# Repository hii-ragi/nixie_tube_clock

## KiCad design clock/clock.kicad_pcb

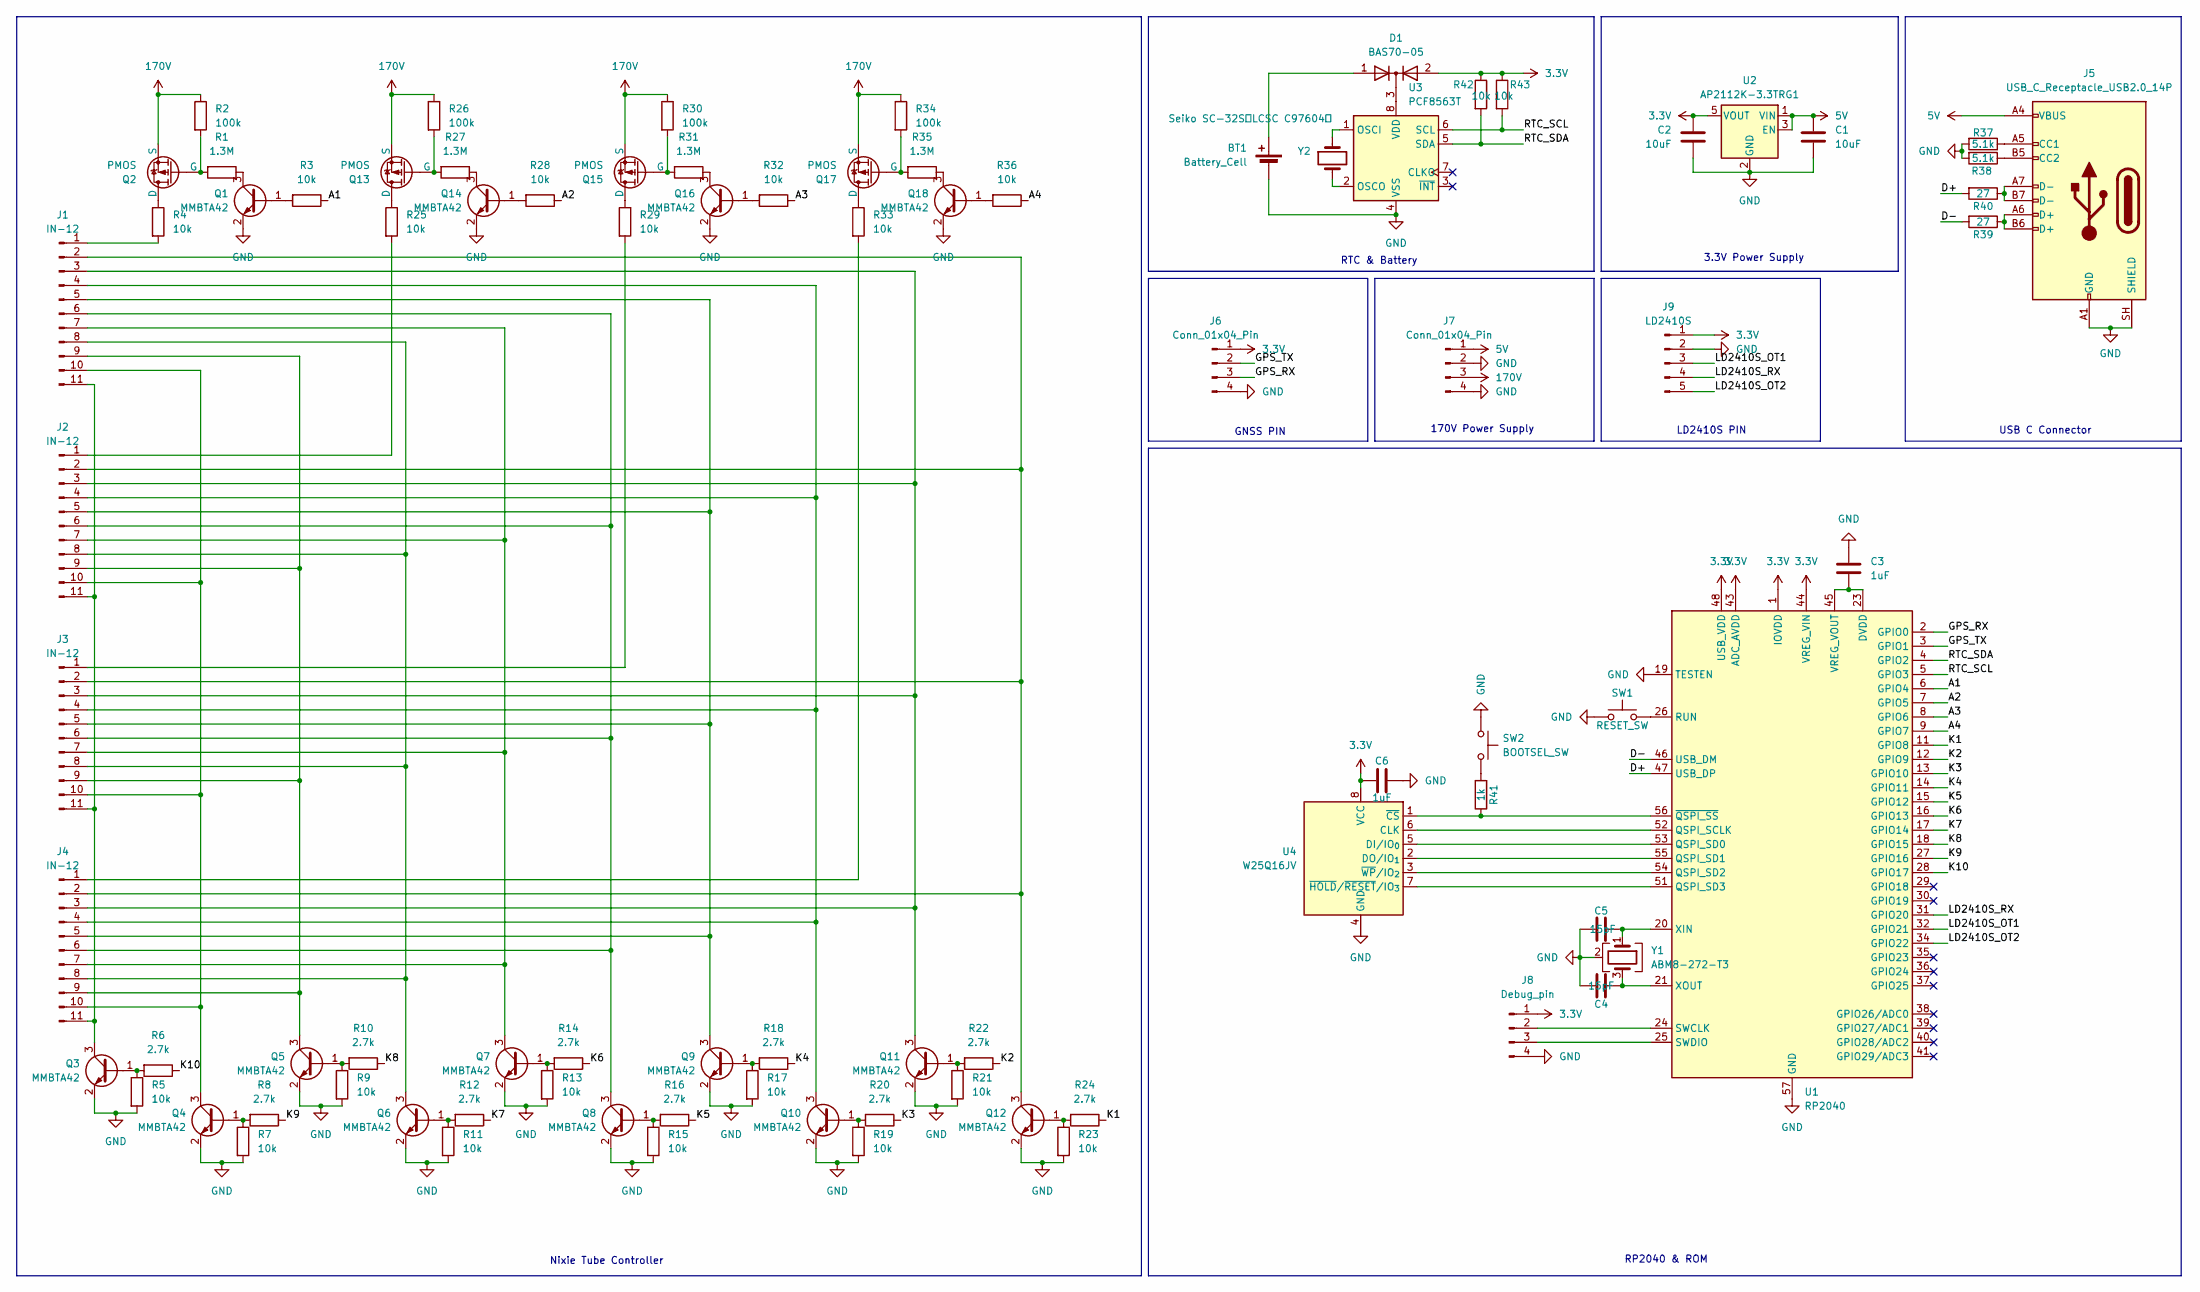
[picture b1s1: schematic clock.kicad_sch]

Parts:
BT1: Battery_Cell
C1, C2: 10uF; C_0603_1608Metric
C3, C6: 1uF; C_0603_1608Metric
C4, C5: 15pF; C_0603_1608Metric
D1: BAS70-05; SOT-23
J1, J2, J3, J4: IN-12
J5: USB_C_Receptacle_USB2.0_14P; USB_C_Receptacle_Palconn_UTC16-G
J6, J7: Conn_01x04_Pin; PinSocket_1x04_P2.54mm_Vertical
J8: Debug_pin; PinSocket_1x04_P2.54mm_Vertical
J9: LD2410S; PinSocket_1x05_P2.54mm_Vertical
Q1, Q3, Q4, Q5, Q6, Q7, Q8, Q9, Q10, Q11, Q12, Q14, Q16, Q18: MMBTA42; SOT-23
Q2, Q13, Q15, Q17: PMOS; SC-59
R1, R27, R31, R35: 1.3M; R_0603_1608Metric
R2, R26, R30, R34: 100k; R_0603_1608Metric
R3, R4, R5, R7, R9, R11, R13, R15, R17, R19, R21, R23, R25, R28, R29, R32, R33, R36, R42, R43: 10k; R_0603_1608Metric
R6, R8, R10, R12, R14, R16, R18, R20, R22, R24: 2.7k; R_0603_1608Metric
R37, R38: 5.1k; R_0603_1608Metric
R39, R40: 27; R_0603_1608Metric
R41: 1k; R_0603_1608Metric
SW1: RESET_SW; SW-SMD_4P-L5.1-W5.1-P3.70-LS6.5-TL_H1.5
SW2: BOOTSEL_SW; SW-SMD_4P-L5.1-W5.1-P3.70-LS6.5-TL_H1.5
U1: RP2040; QFN-56-1EP_7x7mm_P0.4mm_EP3.2x3.2mm
U2: AP2112K-3.3TRG1; SOT-23-5
U3: PCF8563T; SOIC-8_3.9x4.9mm_P1.27mm
U4: W25Q16JV; SOIC-8_5.3x5.3mm_P1.27mm
Y1: ABM8-272-T3; Crystal_SMD_0603-4Pin_6.0x3.5mm
Y2: Seiko SC-32S（LCSC C97604）; Crystal_AT310_D3.0mm_L10.0mm_Horizontal

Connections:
3.3V: C2.1, C6.2, D1.2 (A), J6.1, J8.1, J9.1, R42.1, R43.1, U1.1 (IOVDD), U1.10 (IOVDD), U1.22 (IOVDD), U1.33 (IOVDD), U1.42 (IOVDD), U1.43 (ADC_AVDD), U1.44 (VREG_VIN), U1.48 (USB_VDD), U1.49 (IOVDD), U2.5 (VOUT), U4.8 (VCC)
5V: C1.1, J5.A4 (VBUS), J5.A9 (VBUS), J5.B4 (VBUS), J5.B9 (VBUS), J7.1, U2.1 (VIN), U2.3 (EN)
170V: J7.3, Q2.3 (S), Q13.3 (S), Q15.3 (S), Q17.3 (S), R2.1, R26.1, R30.1, R34.1
/A1: R3.1, U1.6 (GPIO4)
/A2: R28.1, U1.7 (GPIO5)
/A3: R32.1, U1.8 (GPIO6)
/A4: R36.1, U1.9 (GPIO7)
/D+: R40.2, U1.47 (USB_DP)
/D-: R39.2, U1.46 (USB_DM)
/GPS_RX: J6.3, U1.2 (GPIO0)
/GPS_TX: J6.2, U1.3 (GPIO1)
/K1: R24.1, U1.11 (GPIO8)
/K2: R22.1, U1.12 (GPIO9)
/K3: R20.1, U1.13 (GPIO10)
/K4: R18.1, U1.14 (GPIO11)
/K5: R16.1, U1.15 (GPIO12)
/K6: R14.1, U1.16 (GPIO13)
/K7: R12.1, U1.17 (GPIO14)
/K8: R10.1, U1.18 (GPIO15)
/K9: R8.1, U1.27 (GPIO16)
/K10: R6.1, U1.28 (GPIO17)
/LD2410S_OT1: J9.3, U1.32 (GPIO21)
/LD2410S_OT2: J9.5, U1.34 (GPIO22)
/LD2410S_RX: J9.4, U1.31 (GPIO20)
/RTC_SCL: R43.2, U1.5 (GPIO3), U3.6 (SCL)
/RTC_SDA: R42.2, U1.4 (GPIO2), U3.5 (SDA)
GND: BT1.2 (-), C1.2, C2.2, C3.1, C4.2, C5.2, C6.1, J5.A1 (GND), J5.A12 (GND), J5.B1 (GND), J5.B12 (GND), J5.SH (SHIELD), J6.4, J7.2, J7.4, J8.4, J9.2, Q1.2 (E), Q3.2 (E), Q4.2 (E), Q5.2 (E), Q6.2 (E), Q7.2 (E), Q8.2 (E), Q9.2 (E), Q10.2 (E), Q11.2 (E), Q12.2 (E), Q14.2 (E), Q16.2 (E), Q18.2 (E), R5.2, R7.2, R9.2, R11.2, R13.2, R15.2, R17.2, R19.2, R21.2, R23.2, R37.2, R38.2, SW1.1, SW2.1, U1.19 (TESTEN), U1.57 (GND), U2.2 (GND), U3.4 (VSS), U4.4 (GND), Y1.2 (G), Y1.4 (G)
unnamed: BT1.1 (+), D1.1 (A)
unnamed: D1.3 (K), U3.8 (VDD)
unnamed: J1.1, R4.2
unnamed: J1.2, J2.2, J3.2, J4.2, Q12.3 (C)
unnamed: J1.3, J2.3, J3.3, J4.3, Q11.3 (C)
unnamed: J1.4, J2.4, J3.4, J4.4, Q10.3 (C)
unnamed: J1.5, J2.5, J3.5, J4.5, Q9.3 (C)
unnamed: J1.6, J2.6, J3.6, J4.6, Q8.3 (C)
unnamed: J1.7, J2.7, J3.7, J4.7, Q7.3 (C)
unnamed: J1.8, J2.8, J3.8, J4.8, Q6.3 (C)
unnamed: J1.9, J2.9, J3.9, J4.9, Q5.3 (C)
unnamed: J1.10, J2.10, J3.10, J4.10, Q4.3 (C)
unnamed: J1.11, J2.11, J3.11, J4.11, Q3.3 (C)
unnamed: J2.1, R25.2
unnamed: J3.1, R29.2
unnamed: J4.1, R33.2
unnamed: J5.A5 (CC1), R37.1
unnamed: J5.B5 (CC2), R38.1
unnamed: J5.A6 (D+), J5.B6 (D+), R39.1
unnamed: J5.A7 (D-), J5.B7 (D-), R40.1
unnamed: J8.2, U1.24 (SWCLK)
unnamed: J8.3, U1.25 (SWDIO)
unnamed: Q1.1 (B), R3.2
unnamed: Q1.3 (C), R1.1
unnamed: Q2.1 (D), R4.1
unnamed: Q2.2 (G), R1.2, R2.2
unnamed: Q3.1 (B), R5.1, R6.2
unnamed: Q4.1 (B), R7.1, R8.2
unnamed: Q5.1 (B), R9.1, R10.2
unnamed: Q6.1 (B), R11.1, R12.2
unnamed: Q7.1 (B), R13.1, R14.2
unnamed: Q8.1 (B), R15.1, R16.2
unnamed: Q9.1 (B), R17.1, R18.2
unnamed: Q10.1 (B), R19.1, R20.2
unnamed: Q11.1 (B), R21.1, R22.2
unnamed: Q12.1 (B), R23.1, R24.2
unnamed: Q13.1 (D), R25.1
unnamed: Q13.2 (G), R26.2, R27.2
unnamed: Q14.1 (B), R28.2
unnamed: Q14.3 (C), R27.1
unnamed: Q15.1 (D), R29.1
unnamed: Q15.2 (G), R30.2, R31.2
unnamed: Q16.1 (B), R32.2
unnamed: Q16.3 (C), R31.1
unnamed: Q17.1 (D), R33.1
unnamed: Q17.2 (G), R34.2, R35.2
unnamed: Q18.1 (B), R36.2
unnamed: Q18.3 (C), R35.1
unnamed: R41.2, SW2.2
unnamed: U1.52 (QSPI_SCLK), U4.6 (CLK)
unnamed: U1.53 (QSPI_SD0), U4.5 (DI/IO_{0})
unnamed: U1.55 (QSPI_SD1), U4.2 (DO/IO_{1})
unnamed: U1.54 (QSPI_SD2), U4.3 (~WP/IO_{2})
unnamed: U1.51 (QSPI_SD3), U4.7 (~HOLD/~RESET/IO_{3})
unnamed: SW1.2, U1.26 (RUN)
unnamed: C3.2, U1.23 (DVDD), U1.45 (VREG_VOUT), U1.50 (DVDD)
unnamed: C5.1, U1.20 (XIN), Y1.1
unnamed: C4.1, U1.21 (XOUT), Y1.3
unnamed: R41.1, U1.56 (~QSPI_SS), U4.1 (~CS)
unnamed: U3.1 (OSCI), Y2.1
unnamed: U3.2 (OSCO), Y2.2

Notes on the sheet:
USB C Connector
GNSS PIN
Nixie Tube Controller
RP2040 & ROM
RTC & Battery
LD2410S PIN
170V Power Supply
3.3V Power Supply

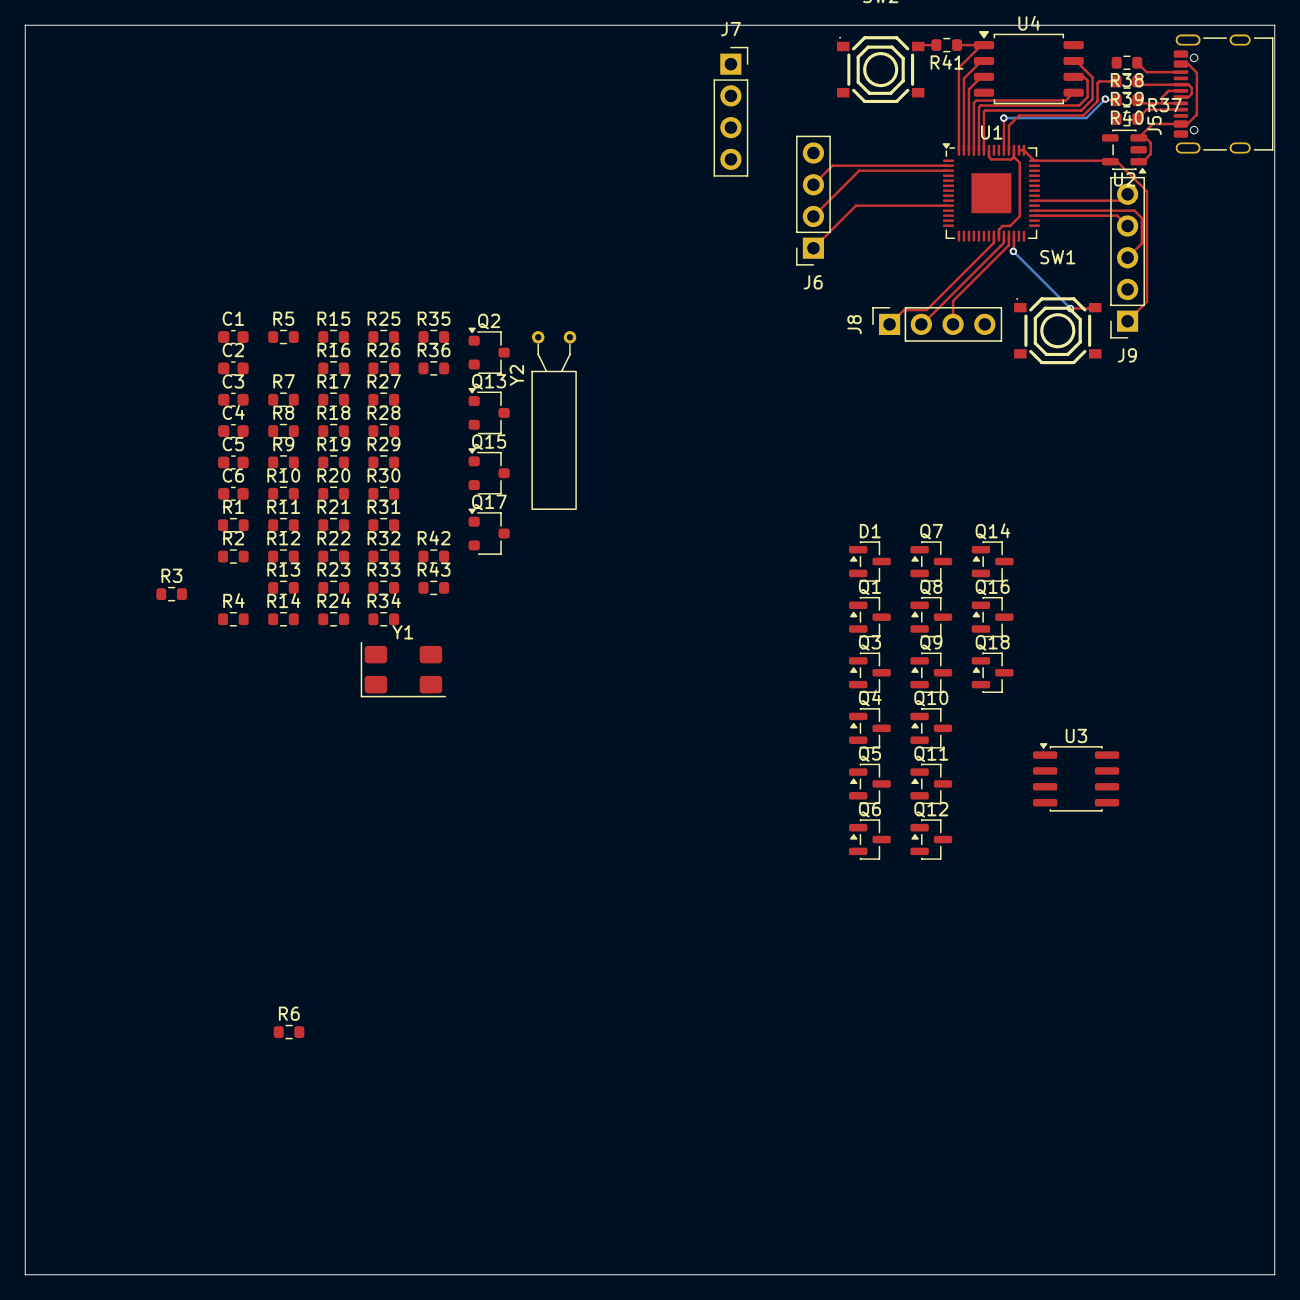
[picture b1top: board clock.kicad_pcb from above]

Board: 2 copper layers, 100.0 x 100.0 mm, 81 parts (0 on the bottom side), 73 nets.
